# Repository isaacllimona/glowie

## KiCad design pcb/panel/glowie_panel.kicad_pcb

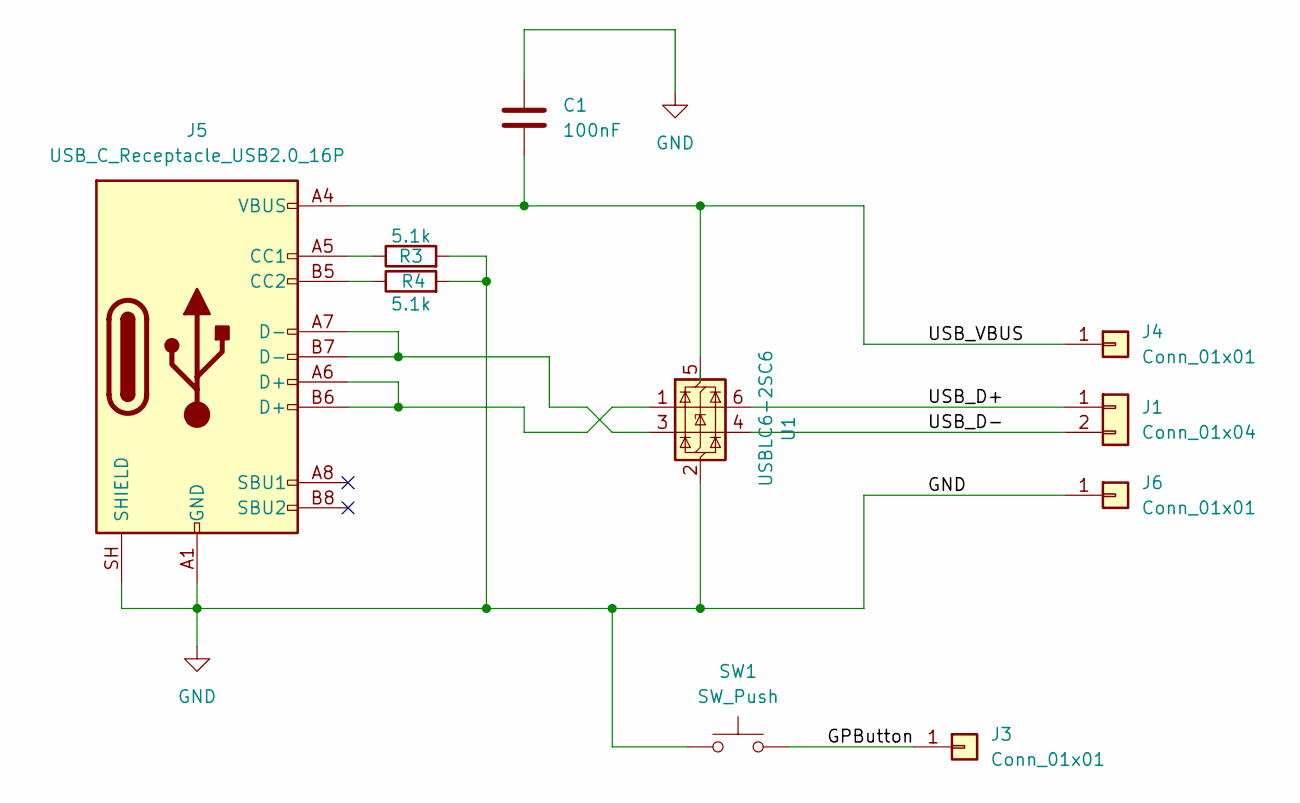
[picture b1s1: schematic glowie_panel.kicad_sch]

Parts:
C1: 100nF; C_0402_1005Metric
J1: Conn_01x04; usb_data_wire_pads
J3: Conn_01x01; SolderWirePad_1x01_SMD_1.5x3mm
J4, J6: Conn_01x01; th_wire_pad_0.9mm
J5: USB_C_Receptacle_USB2.0_16P; CONN_USB4145-03-0230-C_GCT; MPN USB4220-03-1000-C
R3, R4: 5.1k; R_0402_1005Metric; MPN 0402 5.1k
SW1: SW_Push; TACT_PTS815; MPN PTS815 SJG 250 SMTR LFS
U1: USBLC6-2SC6; SOT-23-6; MPN USBLC6-2SC6

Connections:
/GPButton: J3.1 (Pin_1_1), SW1.2
/USB_D+: J1.1, U1.6 (I/O1)
/USB_D-: J1.2, U1.4 (I/O2)
/USB_VBUS: C1.2, J4.1 (Pin_1_1), J5.A4 (VBUS), J5.A9 (VBUS), J5.B4 (VBUS), J5.B9 (VBUS), U1.5 (VBUS)
GND: C1.1, J5.A1 (GND), J5.A12 (GND), J5.B1 (GND), J5.B12 (GND), J5.SH (SHIELD), J6.1 (Pin_1_1), R3.2, R4.2, SW1.1, U1.2 (GND)
unnamed: J5.A5 (CC1), R3.1
unnamed: J5.B5 (CC2), R4.1
unnamed: J5.A6 (D+), J5.B6 (D+), U1.1 (I/O1)
unnamed: J5.A7 (D-), J5.B7 (D-), U1.3 (I/O2)

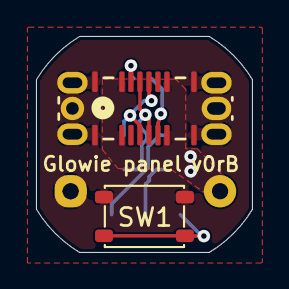
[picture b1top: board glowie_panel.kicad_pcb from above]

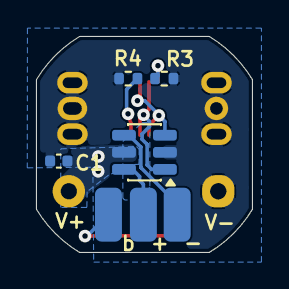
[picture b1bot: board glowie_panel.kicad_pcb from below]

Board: 2 copper layers, 12.0 x 12.0 mm, 10 parts (8 on the bottom side), 9 nets.

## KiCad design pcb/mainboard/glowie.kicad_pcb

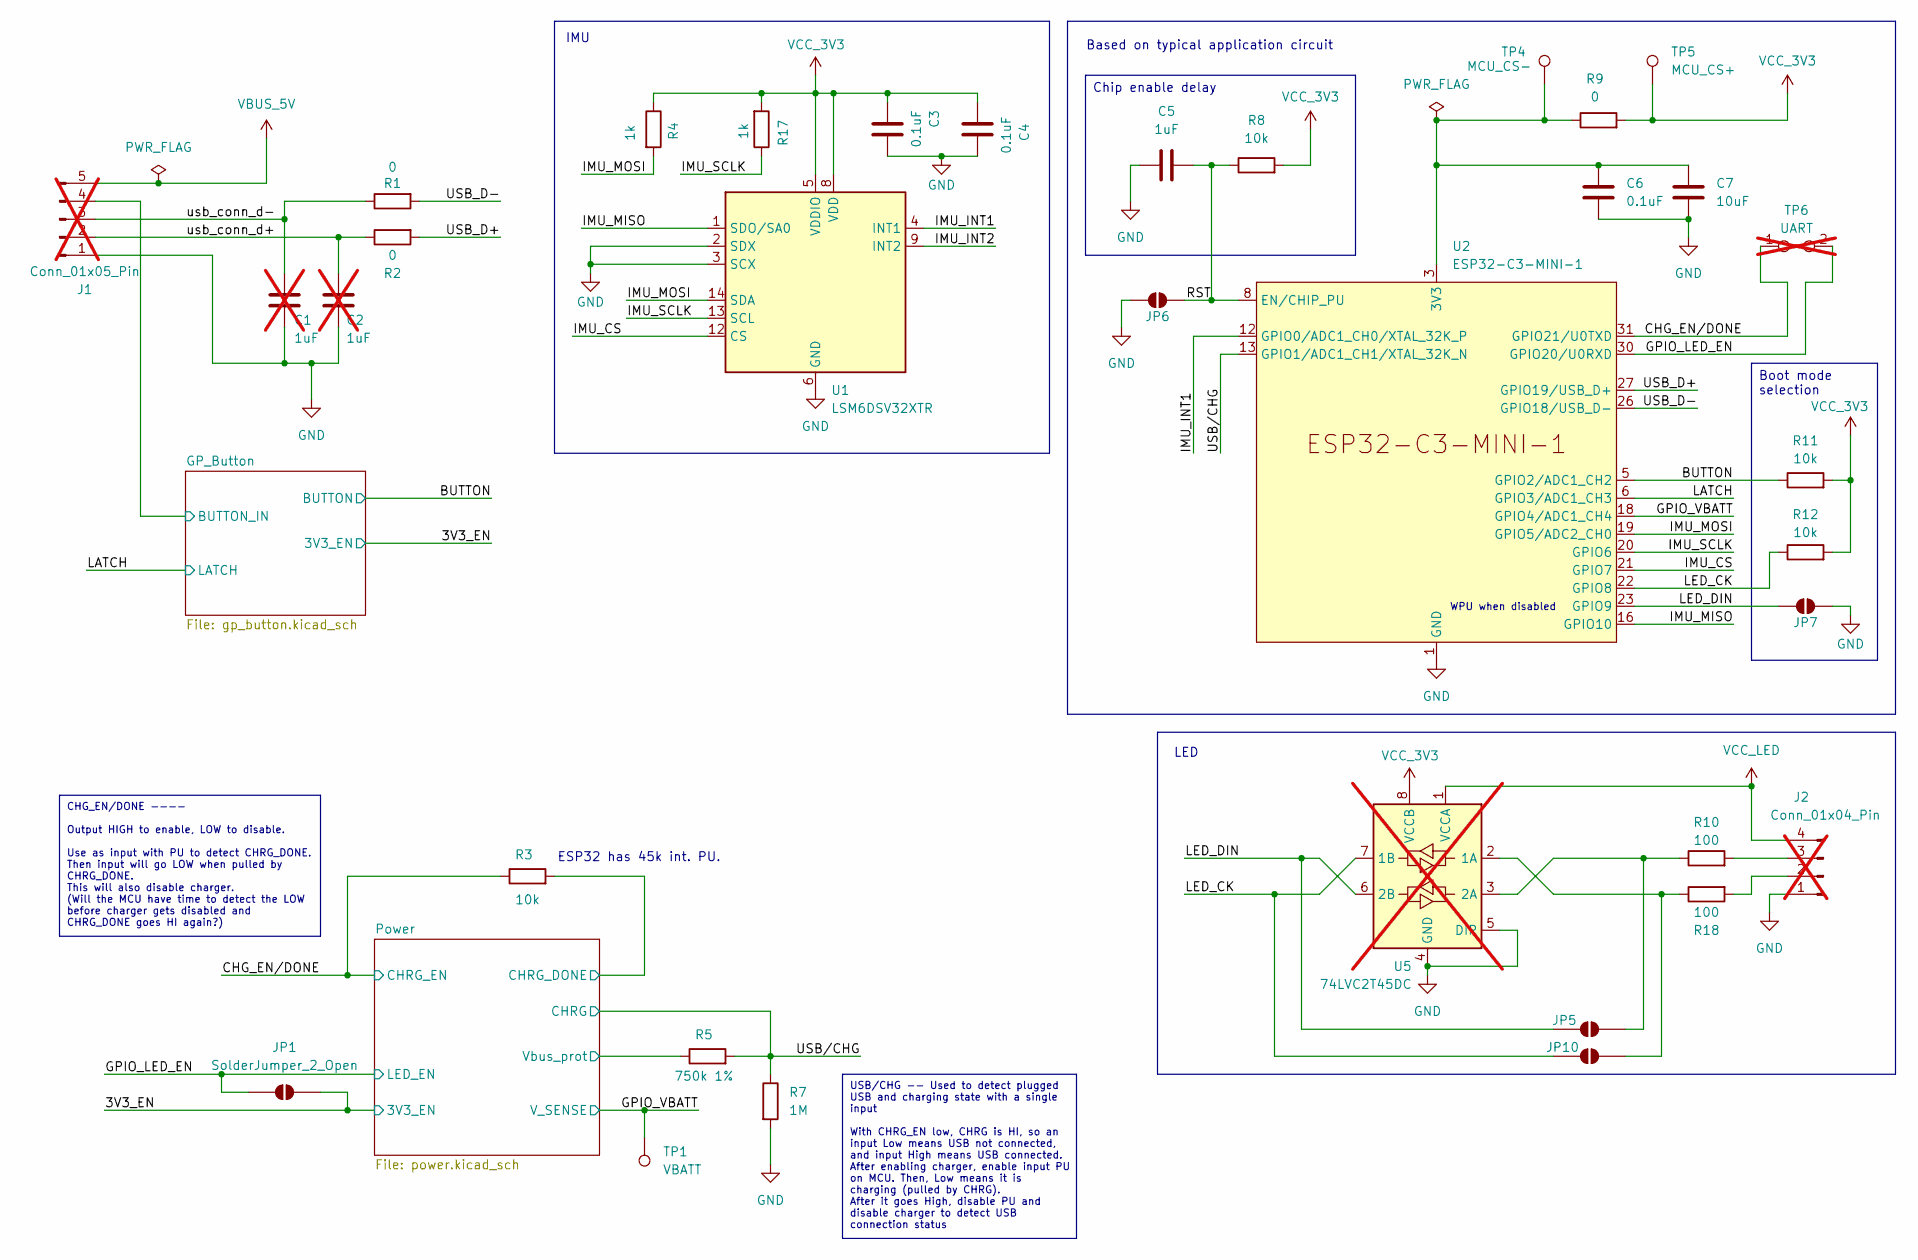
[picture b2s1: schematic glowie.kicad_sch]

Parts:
C1, C2: 1uF; C_0402_1005Metric; not fitted
C3, C4, C6: 0.1uF; C_0402_1005Metric
C5: 1uF; C_0402_1005Metric
C7: 10uF; C_0402_1005Metric
J1: Conn_01x05_Pin; PinHeader_1x05_P2.00mm_Vertical; not fitted
J2: Conn_01x04_Pin; PinHeader_1x04_P2.00mm_Vertical; not fitted
JP1, JP5, JP10: SolderJumper_2_Open; SolderJumper
JP6, JP7: SolderJumper_2_Open; SolderJumper-2_P1.3mm_Open_RoundedPad1.0x1.5mm
R1, R2: 0; R_0402_1005Metric; MPN 0402 33
R3, R8, R11, R12: 10k; R_0402_1005Metric; MPN 0402 10k
R4, R17: 1k; R_0402_1005Metric_Pad0.72x0.64mm_HandSolder; MPN 0402 1k
R5: 750k 1%; R_0402_1005Metric; MPN 0402 750k
R7: 1M; R_0402_1005Metric; MPN 0402 1M
R9: 0; R_0402_1005Metric_Pad0.72x0.64mm_HandSolder; MPN 0402 10k
R10, R18: 100; R_0402_1005Metric
TP1: VBATT; TestPoint_Pad_D1.0mm
TP4: MCU_CS-; TestPoint_Pad_D1.0mm
TP5: MCU_CS+; TestPoint_Pad_D1.0mm
TP6: UART; PinHeader_1x02_P2.00mm_Vertical; not fitted
U1: LSM6DSV32XTR; LGA-14_3x2.5mm_P0.5mm_LayoutBorder3x4y; MPN LSM6DSV32XTR
U2: ESP32-C3-MINI-1; MPN ESP32-C3-MINI-1
U5: 74LVC2T45DC; VSSOP-8_2.3x2mm_P0.5mm; not fitted

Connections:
/3V3_EN: JP1.1 (A); also elsewhere on the board
/BUTTON: R11.1, U2.5 (GPIO2/ADC1_CH2); also elsewhere on the board
/CHG_EN/DONE: R3.1, TP6.1, U2.31 (GPIO21/U0TXD); also elsewhere on the board
/GPIO_LED_EN: JP1.2 (B), TP6.2, U2.30 (GPIO20/U0RXD); also elsewhere on the board
/GPIO_VBATT: TP1.1 (1_1), U2.18 (GPIO4/ADC1_CH4); also elsewhere on the board
/GP_Button/BUTTON_IN: J1.4; also elsewhere on the board
/IMU_CS: U1.12 (CS), U2.21 (GPIO7)
/IMU_INT1: U1.4 (INT1), U2.12 (GPIO0/ADC1_CH0/XTAL_32K_P)
/IMU_INT2: U1.9 (INT2)
/IMU_MISO: U1.1 (SDO/SA0), U2.16 (GPIO10)
/IMU_MOSI: R4.2, U1.14 (SDA), U2.19 (GPIO5/ADC2_CH0)
/IMU_SCLK: R17.1, U1.13 (SCL), U2.20 (GPIO6)
/LATCH: U2.6 (GPIO3/ADC1_CH3); also elsewhere on the board
/LED_CK: JP10.1 (A), R12.1, U2.22 (GPIO8), U5.7 (1B)
/LED_DIN: JP5.1 (A), JP7.1 (A), U2.23 (GPIO9), U5.6 (2B)
/Power/CHRG_DONE: R3.2; also elsewhere on the board
/Power/Vbus_prot: R5.1; also elsewhere on the board
/RST: C5.2, JP6.2 (B), R8.1, U2.8 (EN/CHIP_PU)
/USB_D+: R2.2, U2.27 (GPIO19/USB_D+)
/USB_D-: R1.2, U2.26 (GPIO18/USB_D-)
/USB/CHG: R5.2, R7.1, U2.13 (GPIO1/ADC1_CH1/XTAL_32K_N); also elsewhere on the board
/usb_conn_d+: C2.2, J1.2, R2.1
/usb_conn_d-: C1.2, J1.3, R1.1
GND: C1.1, C2.1, C3.1, C4.2, C5.1, C6.2, C7.2, J1.1, J2.1, JP6.1 (A), JP7.2 (B), R7.2, U1.2 (SDX), U1.3 (SCX), U1.6 (GND), U1.7 (GND), U2.1 (GND), U2.2 (GND), U2.11 (GND), U2.14 (GND), U2.36 (GND), U2.37 (GND), U2.38 (GND), U2.39 (GND), U2.40 (GND), U2.41 (GND), U2.42 (GND), U2.43 (GND), U2.44 (GND), U2.45 (GND), U2.46 (GND), U2.47 (GND), U2.48 (GND), U2.49 (GND), U2.50 (GND), U2.51 (GND), U2.52 (GND), U2.53 (GND), U5.4 (GND), U5.5 (DIR); also elsewhere on the board
unnamed: J2.2, R18.2
unnamed: J2.3, R10.2
unnamed: JP5.2 (B), R10.1, U5.3 (2A)
unnamed: JP10.2 (B), R18.1, U5.2 (1A)
unnamed: C6.1, C7.1, R9.1, TP4.1 (1_1), U2.3 (3V3)
VBUS_5V: J1.5; also elsewhere on the board
VCC_3V3: C3.2, C4.1, R4.1, R8.2, R9.2, R11.2, R12.2, R17.2, TP5.1 (1_1), U1.5 (VDDIO), U1.8 (VDD), U5.8 (VCCB); also elsewhere on the board
VCC_LED: J2.4, U5.1 (VCCA); also elsewhere on the board

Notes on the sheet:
WPU when disabled
IMU
Based on typical application circuit
LED
ESP32 has 45k int. PU.
Boot mode selection
Chip enable delay
USB/CHG -- Used to detect plugged USB and charging state with a single input With CHRG_EN low, CHRG is HI, so an input Low means USB not connected, and input High means USB connected. After enabling charger, enable input PU on MCU. Then, Low means it is charging (pulled by CHRG). After it goes High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
CHG_EN/DONE ---- Output HIGH to enable, LOW to disable. Use as input with PU to detect CHRG_DONE. Then input will go LOW when pulled by CHRG_DONE. This will also disable charger. (Will the MCU have time to detect the LOW before charger gets disabled and CHRG_DONE goes HI again?)

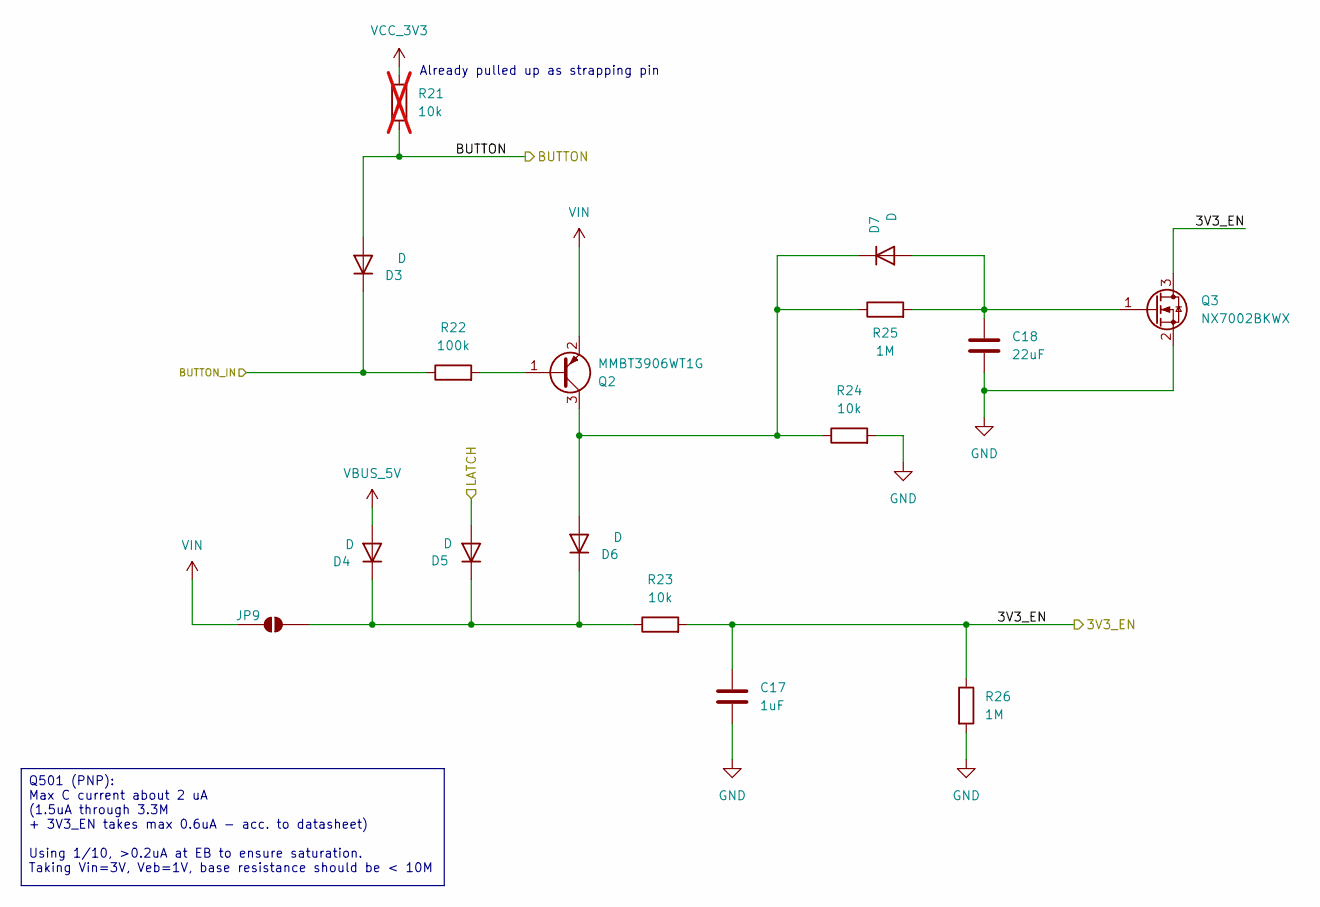
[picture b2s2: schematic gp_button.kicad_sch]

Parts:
C17: 1uF; C_0402_1005Metric_Pad0.74x0.62mm_HandSolder
C18: 22uF; C_0603_1608Metric
D3, D4, D5, D6, D7: D; D_SOD-882D; MPN 0402
JP9: SolderJumper_2_Open; SolderJumper
Q2: MMBT3906WT1G; SOT-323_SC-70; MPN MMBT3906WT1G
Q3: NX7002BKWX; SOT-323_SC-70
R21: 10k; R_0402_1005Metric; not fitted
R22: 100k; R_0402_1005Metric; MPN 0402 1M
R23, R24: 10k; R_0402_1005Metric; MPN 0402 2M
R25: 1M; R_0402_1005Metric_Pad0.72x0.64mm_HandSolder; MPN 0402 3.3M 1%
R26: 1M; R_0402_1005Metric; MPN 0402 1M

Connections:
/3V3_EN: C17.2, Q3.3 (D), R23.2, R26.1; also elsewhere on the board
/BUTTON: D3.2 (A), R21.2; also elsewhere on the board
/GP_Button/BUTTON_IN: D3.1 (K), R22.1; also elsewhere on the board
/LATCH: D5.2 (A); also elsewhere on the board
GND: C17.1, C18.1, Q3.2 (S), R24.2, R26.2; also elsewhere on the board
unnamed: D4.1 (K), D5.1 (K), D6.1 (K), JP9.2 (B), R23.1
unnamed: D6.2 (A), D7.1 (K), Q2.3 (C), R24.1, R25.1
unnamed: C18.2, D7.2 (A), Q3.1 (G), R25.2
unnamed: Q2.1 (B), R22.2
VBUS_5V: D4.2 (A); also elsewhere on the board
VIN: JP9.1 (A), Q2.2 (E); also elsewhere on the board

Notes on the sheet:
Already pulled up as strapping pin
Q501 (PNP): Max C current about 2 uA (1.5uA through 3.3M + 3V3_EN takes max 0.6uA - acc. to datasheet) Using 1/10, >0.2uA at EB to ensure saturation. Taking Vin=3V, Veb=1V, base resistance should be < 10M

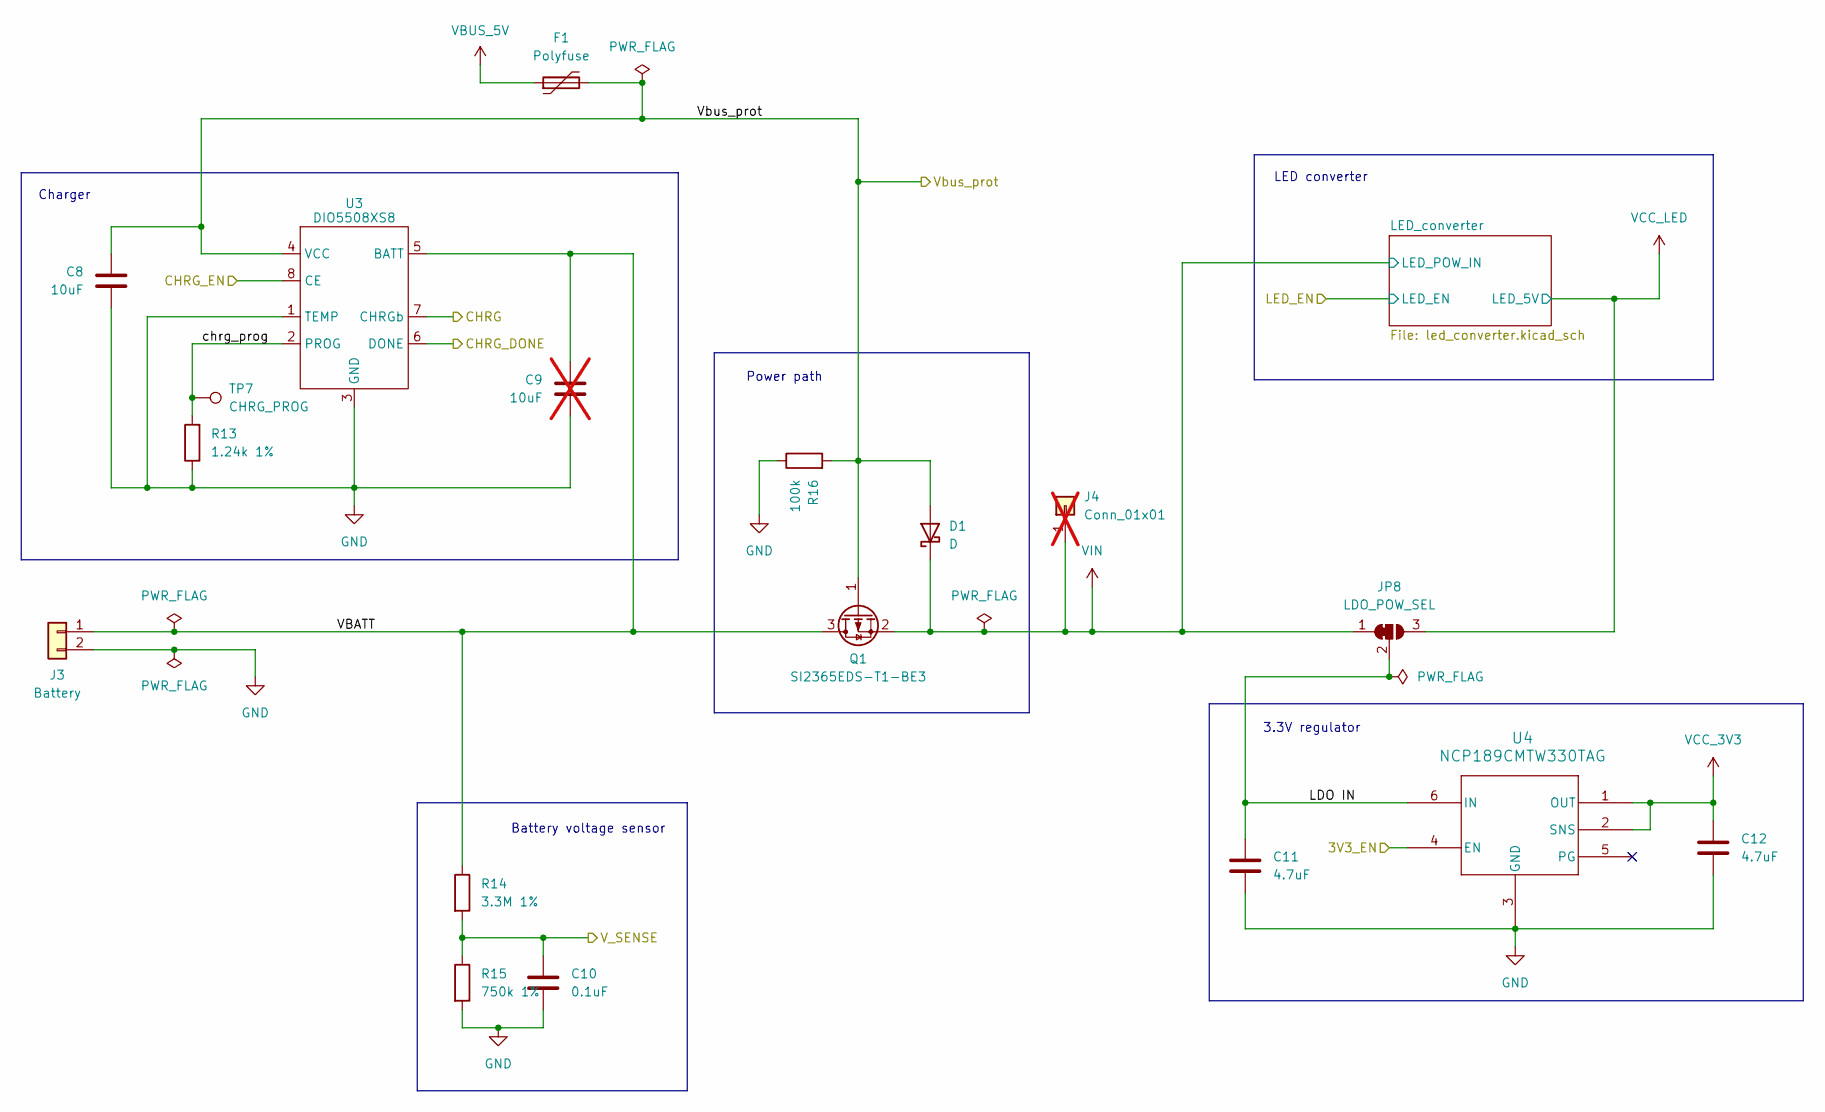
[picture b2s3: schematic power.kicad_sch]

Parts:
C8: 10uF; C_0402_1005Metric
C9: 10uF; C_0402_1005Metric; not fitted
C10: 0.1uF; C_0402_1005Metric
C11, C12: 4.7uF; C_0402_1005Metric
D1: D; D_SMA; MPN SK34SMA-3G
F1: Polyfuse; Fuse_0603_1608Metric; MPN ERBRE2R00V
J3: Battery; CONN_B02B-PASK-1_JST
J4: Conn_01x01; SolderWire-0.5sqmm_1x01_D0.9mm_OD2.1mm; not fitted
JP8: LDO_POW_SEL; SolderJumper-3_P1.3mm_Bridged12_RoundedPad1.0x1.5mm
Q1: SI2365EDS-T1-BE3; SOT-23; MPN SI2365EDS-T1-BE3
R13: 1.24k 1%; R_0402_1005Metric_Pad0.72x0.64mm_HandSolder; MPN 0402 1.5k
R14: 3.3M 1%; R_0402_1005Metric; MPN 0402 3.3M 1%
R15: 750k 1%; R_0402_1005Metric; MPN 0402 750k
R16: 100k; R_0402_1005Metric; MPN 0402 1M
TP7: CHRG_PROG; TestPoint_Pad_D1.0mm
U3: DIO5508XS8; SOIC-8-1EP_3.9x4.9mm_P1.27mm_EP2.41x3.81mm; MPN DIO5508XS8
U4: NCP189CMTW330TAG; NCP189; MPN NCP189CMTW330TAG

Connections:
/3V3_EN: U4.4 (EN); also elsewhere on the board
/CHG_EN/DONE: U3.8 (CE); also elsewhere on the board
/GPIO_VBATT: C10.1, R14.2, R15.1; also elsewhere on the board
/Power/CHRG_DONE: U3.6 (DONE); also elsewhere on the board
/Power/LDO IN: C11.1, JP8.2 (C), U4.6 (IN)
/Power/VBATT: C9.1, J3.1, Q1.3 (D), R14.1, U3.5 (BATT)
/Power/Vbus_prot: C8.1, D1.2 (A), F1.2, Q1.1 (G), R16.2, U3.4 (VCC); also elsewhere on the board
/Power/chrg_prog: R13.2, TP7.1 (1_1), U3.2 (PROG)
/USB/CHG: U3.7 (CHRGb); also elsewhere on the board
GND: C8.2, C9.2, C10.2, C11.2, C12.2, J3.2, R13.1, R15.2, R16.1, U3.1 (TEMP), U3.3 (GND), U3.9, U4.3 (GND), U4.7 (EPAD); also elsewhere on the board
VBUS_5V: F1.1; also elsewhere on the board
VCC_3V3: C12.1, U4.1 (OUT), U4.2 (SNS); also elsewhere on the board
VCC_LED: JP8.3 (B); also elsewhere on the board
VIN: D1.1 (K), J4.1 (Pin_1_1), JP8.1 (A), Q1.2 (S); also elsewhere on the board

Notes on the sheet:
Battery voltage sensor
3.3V regulator
LED converter
Power path
Charger

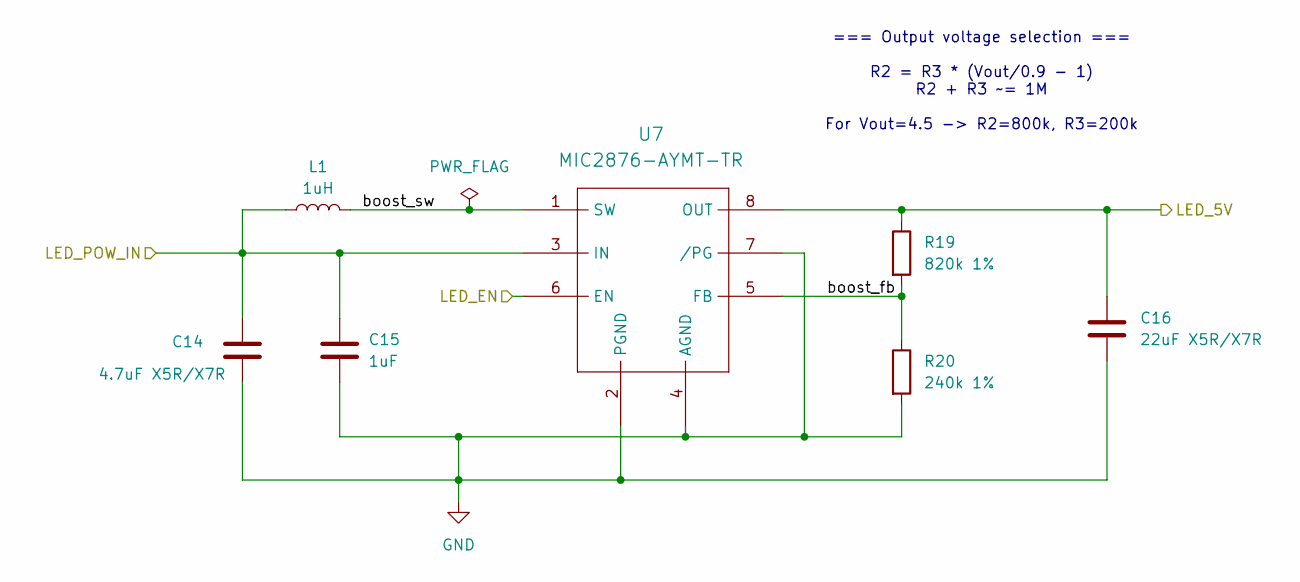
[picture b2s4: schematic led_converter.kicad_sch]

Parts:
C14: 4.7uF X5R/X7R; C_0402_1005Metric
C15: 1uF; C_0402_1005Metric
C16: 22uF X5R/X7R; C_0603_1608Metric
L1: 1uH; Inductor_SRP3212; MPN SRP3212-1R0M
R19: 820k 1%; R_0402_1005Metric_Pad0.72x0.64mm_HandSolder
R20: 240k 1%; R_0402_1005Metric_Pad0.72x0.64mm_HandSolder
U7: MIC2876-AYMT-TR; UDFN8_2X2_MCH-L; MPN MIC2876-AYMT-TR

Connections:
/GPIO_LED_EN: U7.6 (EN); also elsewhere on the board
/Power/LED_converter/boost_fb: R19.2, R20.1, U7.5 (FB)
/Power/LED_converter/boost_sw: L1.2, U7.1 (SW)
GND: C14.2, C15.2, C16.2, R20.2, U7.2 (PGND), U7.4 (AGND), U7.7 (/PG), U7.9 (AGND); also elsewhere on the board
VCC_LED: C16.1, R19.1, U7.8 (OUT); also elsewhere on the board
VIN: C14.1, C15.1, L1.1, U7.3 (IN); also elsewhere on the board

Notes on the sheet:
=== Output voltage selection === R2 = R3 * (Vout/0.9 - 1) R2 + R3 ~= 1M For Vout=4.5 -> R2=800k, R3=200k

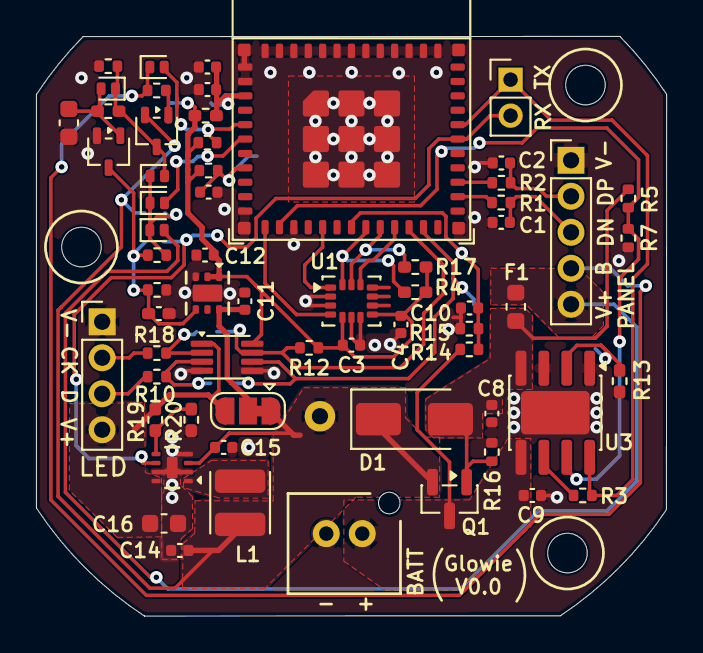
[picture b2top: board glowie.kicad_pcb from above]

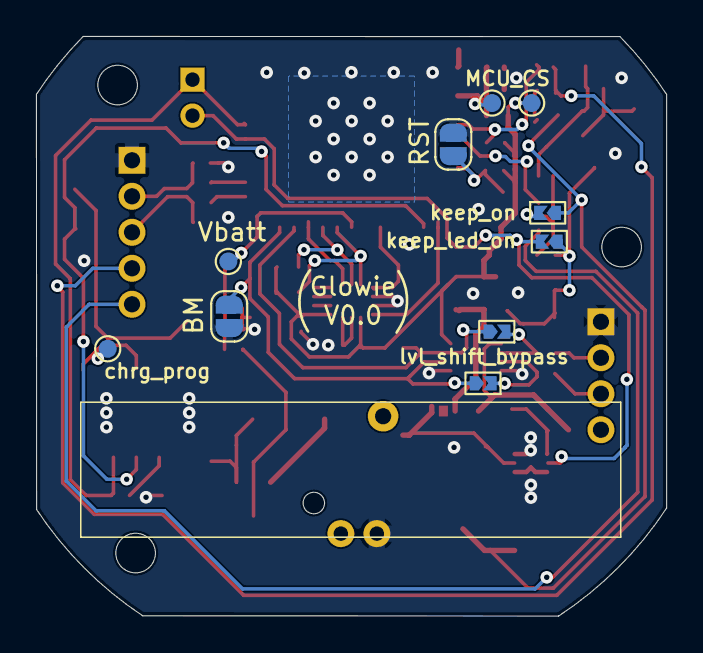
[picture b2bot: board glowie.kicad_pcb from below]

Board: 2 copper layers, 35.0 x 32.2 mm, 74 parts (10 on the bottom side), 41 nets.

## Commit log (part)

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2026-06-01 Add main glowie PCB
2026-06-01 Add panel pcb
2026-06-02 Move PCB things to pcb subdirectory
